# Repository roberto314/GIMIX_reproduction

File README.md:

# GIMIX_reproduction

This Repository is for primarily my GIMIX Ghost Reproduction and various SS-30 and SS-50 Cards.

- GIMIX DMA SASI board finished, no PALs, production ready, gerbers exported

- GIMIX DMA SASI board production version, second Regulator added

- GIMIX dumb two port serial board finished, no PALs, production possible

- Tanner 64k SRAM board finished, no PALs, production possible

- GIMIX Baud Rate Generator Board finished, no PALs, production possible

- GIMIX Floppy DMA finished, no PALs, production possible but not recommended - use production version

- GIMIX Floppy DMA ready for production, cleanup, different routing

- GIMIX intelligent 3-port Serial IO Processor finished (RS232 Transceiver are missing), PAL Contents missing, Firmware found.

- GIMIX Motherboard with onboard Baudrate generator, done, production possible

- GIMIX Motherboard without onboard Baudrate generator, done, production possible

- GIMIX 256k SRAM done, PAL missing but should not be too difficult to figure out, production possible, mods for 62256 chips instead of original 6264. Battery backup won't work with 62256 chips!

- GIMIX 6809 CPU Plus - done, production NOT possible, redesign with GAL or fast EPROM needed, FPLA Contents missing

- GIMIX 6809 CPU Plus Plus - done, This is a production version of the CPU+ board. Changes are: fast EPROM instead of FPLA, one of the four EPROM Sockets is now for a 28-pin EPROM

- GIMIX CRC Generator board - work started but PAL contents missing, schematic missing (a couple of traces need testing), production NOT possible

- GIMIX 6809 CPU III - layout finished but PAL contents missing (some may be registerd - GMX 010 type), production NOT possible

- GIMIX Ghost 6800 - layout finished but some ICs are very rare, production might not be sensible, maybe a redesign with more available components.

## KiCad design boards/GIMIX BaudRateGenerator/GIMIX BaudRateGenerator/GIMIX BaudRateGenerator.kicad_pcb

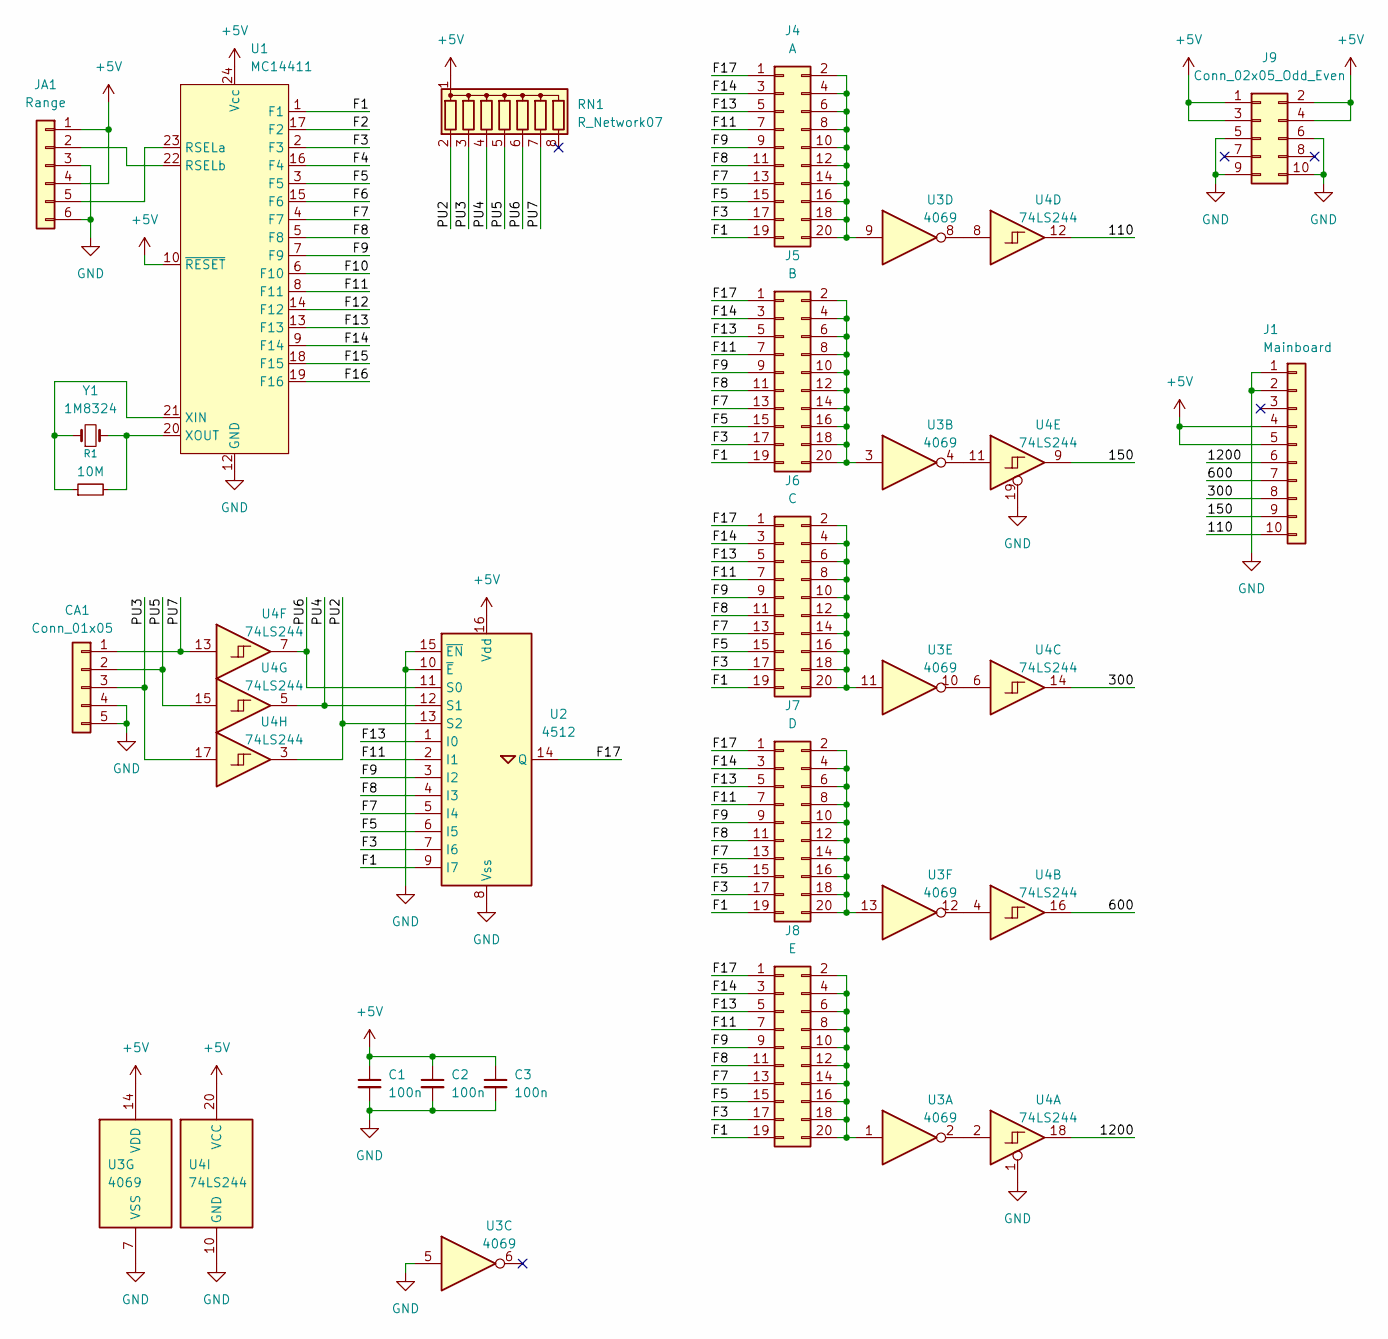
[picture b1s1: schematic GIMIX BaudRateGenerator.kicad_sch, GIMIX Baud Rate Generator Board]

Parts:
C1, C2, C3: 100n; C_Disc_D3.8mm_W2.6mm_P2.50mm
CA1: Conn_01x05; PinHeader_1x05_P2.54mm_Vertical
J1: Mainboard; SS-10_new
J4: A; PinHeader_2x10_P2.54mm_Vertical
J5: B; PinHeader_2x10_P2.54mm_Vertical
J6: C; PinHeader_2x10_P2.54mm_Vertical
J7: D; PinHeader_2x10_P2.54mm_Vertical
J8: E; PinHeader_2x10_P2.54mm_Vertical
J9: Conn_02x05_Odd_Even; PinHeader_2x05_P2.54mm_Vertical
JA1: Range; PinHeader_1x06_P2.54mm_Vertical
R1: 10M; R_Axial_DIN0207_L6.3mm_D2.5mm_P10.16mm_Horizontal
RN1: R_Network07; R_Array_SIP8
U1: MC14411; DIP-24_W15.24mm
U2: 4512; DIP-16_W7.62mm
U3: 4069; DIP-14_W7.62mm
U4: 74LS244; DIP-20_W7.62mm
Y1: 1M8324; Crystal_HC33-U_Horizontal

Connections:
+5V: C1.1, C2.1, C3.1, J1.4, J1.5, J9.1, J9.2, J9.3, J9.4, JA1.1, JA1.4, RN1.1 (common), U1.10 (~RESET), U1.24 (Vcc), U2.16 (Vdd), U3.14 (VDD), U4.20 (VCC)
/110: J1.10, U4.12
/150: J1.9, U4.9
/300: J1.8, U4.14
/600: J1.7, U4.16
/1200: J1.6, U4.18
/F1: J4.19, J5.19, J6.19, J7.19, J8.19, U1.1 (F1), U2.9 (I7)
/F2: U1.17 (F2)
/F3: J4.17, J5.17, J6.17, J7.17, J8.17, U1.2 (F3), U2.7 (I6)
/F4: U1.16 (F4)
/F5: J4.15, J5.15, J6.15, J7.15, J8.15, U1.3 (F5), U2.6 (I5)
/F6: U1.15 (F6)
/F7: J4.13, J5.13, J6.13, J7.13, J8.13, U1.4 (F7), U2.5 (I4)
/F8: J4.11, J5.11, J6.11, J7.11, J8.11, U1.5 (F8), U2.4 (I3)
/F9: J4.9, J5.9, J6.9, J7.9, J8.9, U1.7 (F9), U2.3 (I2)
/F10: U1.6 (F10)
/F11: J4.7, J5.7, J6.7, J7.7, J8.7, U1.8 (F11), U2.2 (I1)
/F12: U1.14 (F12)
/F13: J4.5, J5.5, J6.5, J7.5, J8.5, U1.13 (F13), U2.1 (I0)
/F14: J4.3, J5.3, J6.3, J7.3, J8.3, U1.9 (F14)
/F15: U1.18 (F15)
/F16: U1.19 (F16)
/F17: J4.1, J5.1, J6.1, J7.1, J8.1, U2.14 (Q)
/PU2: RN1.2 (R1), U2.13 (S2), U4.3
/PU3: CA1.3, RN1.3 (R2), U4.17
/PU4: RN1.4 (R3), U2.12 (S1), U4.5
/PU5: CA1.2, RN1.5 (R4), U4.15
/PU6: RN1.6 (R5), U2.11 (S0), U4.7
/PU7: CA1.1, RN1.7 (R6), U4.13
GND: C1.2, C2.2, C3.2, CA1.4, CA1.5, J1.1, J1.2, J9.5, J9.6, J9.9, J9.10, JA1.3, JA1.6, U1.12 (GND), U2.8 (Vss), U2.10 (~E), U2.15 (~EN), U3.5, U3.7 (VSS), U4.1, U4.10 (GND), U4.19
unnamed: J4.2, J4.4, J4.6, J4.8, J4.10, J4.12, J4.14, J4.16, J4.18, J4.20, U3.9
unnamed: J5.2, J5.4, J5.6, J5.8, J5.10, J5.12, J5.14, J5.16, J5.18, J5.20, U3.3
unnamed: J6.2, J6.4, J6.6, J6.8, J6.10, J6.12, J6.14, J6.16, J6.18, J6.20, U3.11
unnamed: J7.2, J7.4, J7.6, J7.8, J7.10, J7.12, J7.14, J7.16, J7.18, J7.20, U3.13
unnamed: J8.2, J8.4, J8.6, J8.8, J8.10, J8.12, J8.14, J8.16, J8.18, J8.20, U3.1
unnamed: JA1.2, U1.22 (RSELb)
unnamed: JA1.5, U1.23 (RSELa)
unnamed: R1.1, U1.21 (XIN), Y1.1
unnamed: R1.2, U1.20 (XOUT), Y1.2
unnamed: U3.2, U4.2
unnamed: U3.4, U4.11
unnamed: U3.8, U4.8
unnamed: U3.10, U4.6
unnamed: U3.12, U4.4

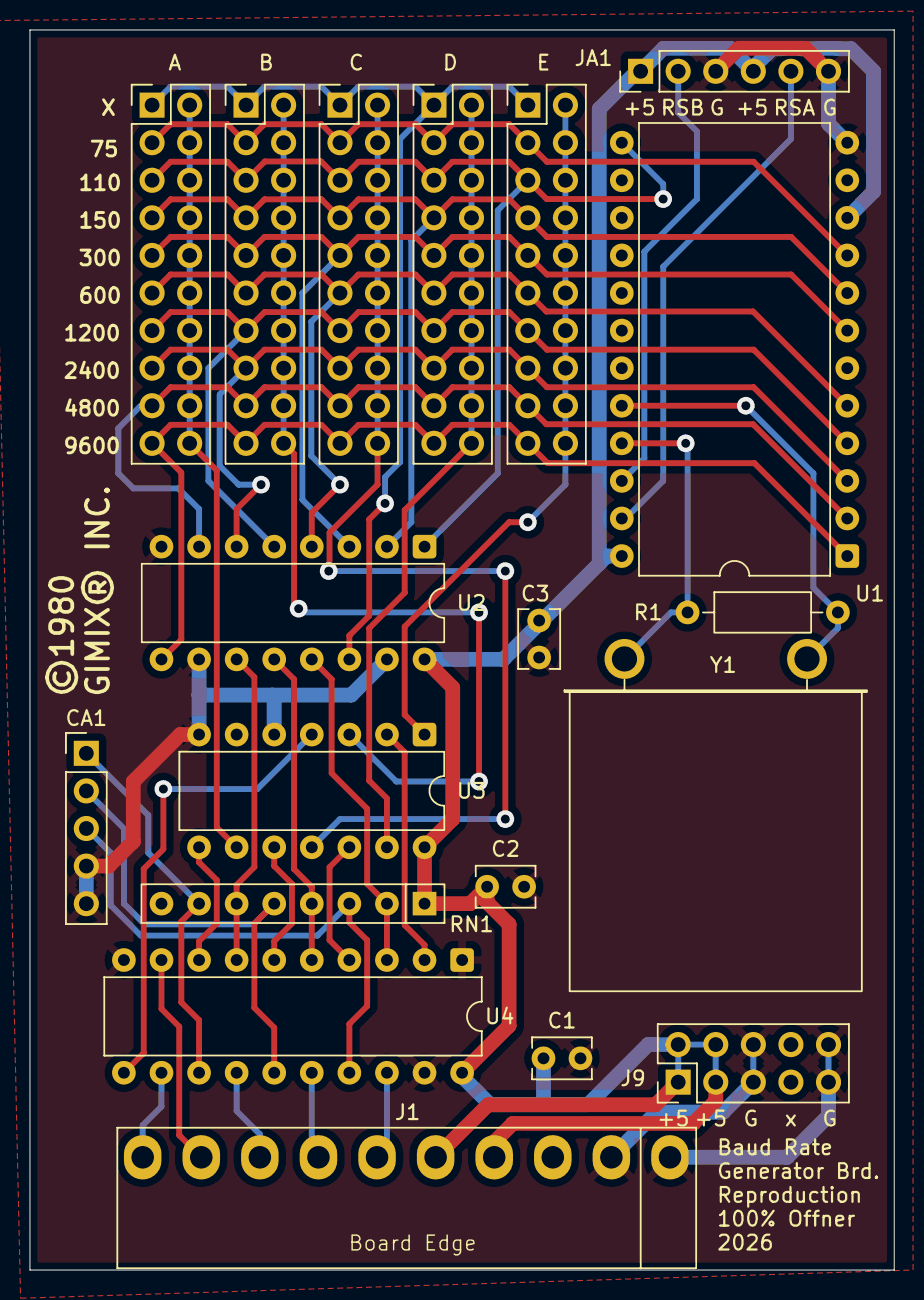
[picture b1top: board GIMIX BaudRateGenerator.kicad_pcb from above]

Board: 2 copper layers, 58.4 x 83.8 mm, 19 parts (0 on the bottom side), 37 nets.

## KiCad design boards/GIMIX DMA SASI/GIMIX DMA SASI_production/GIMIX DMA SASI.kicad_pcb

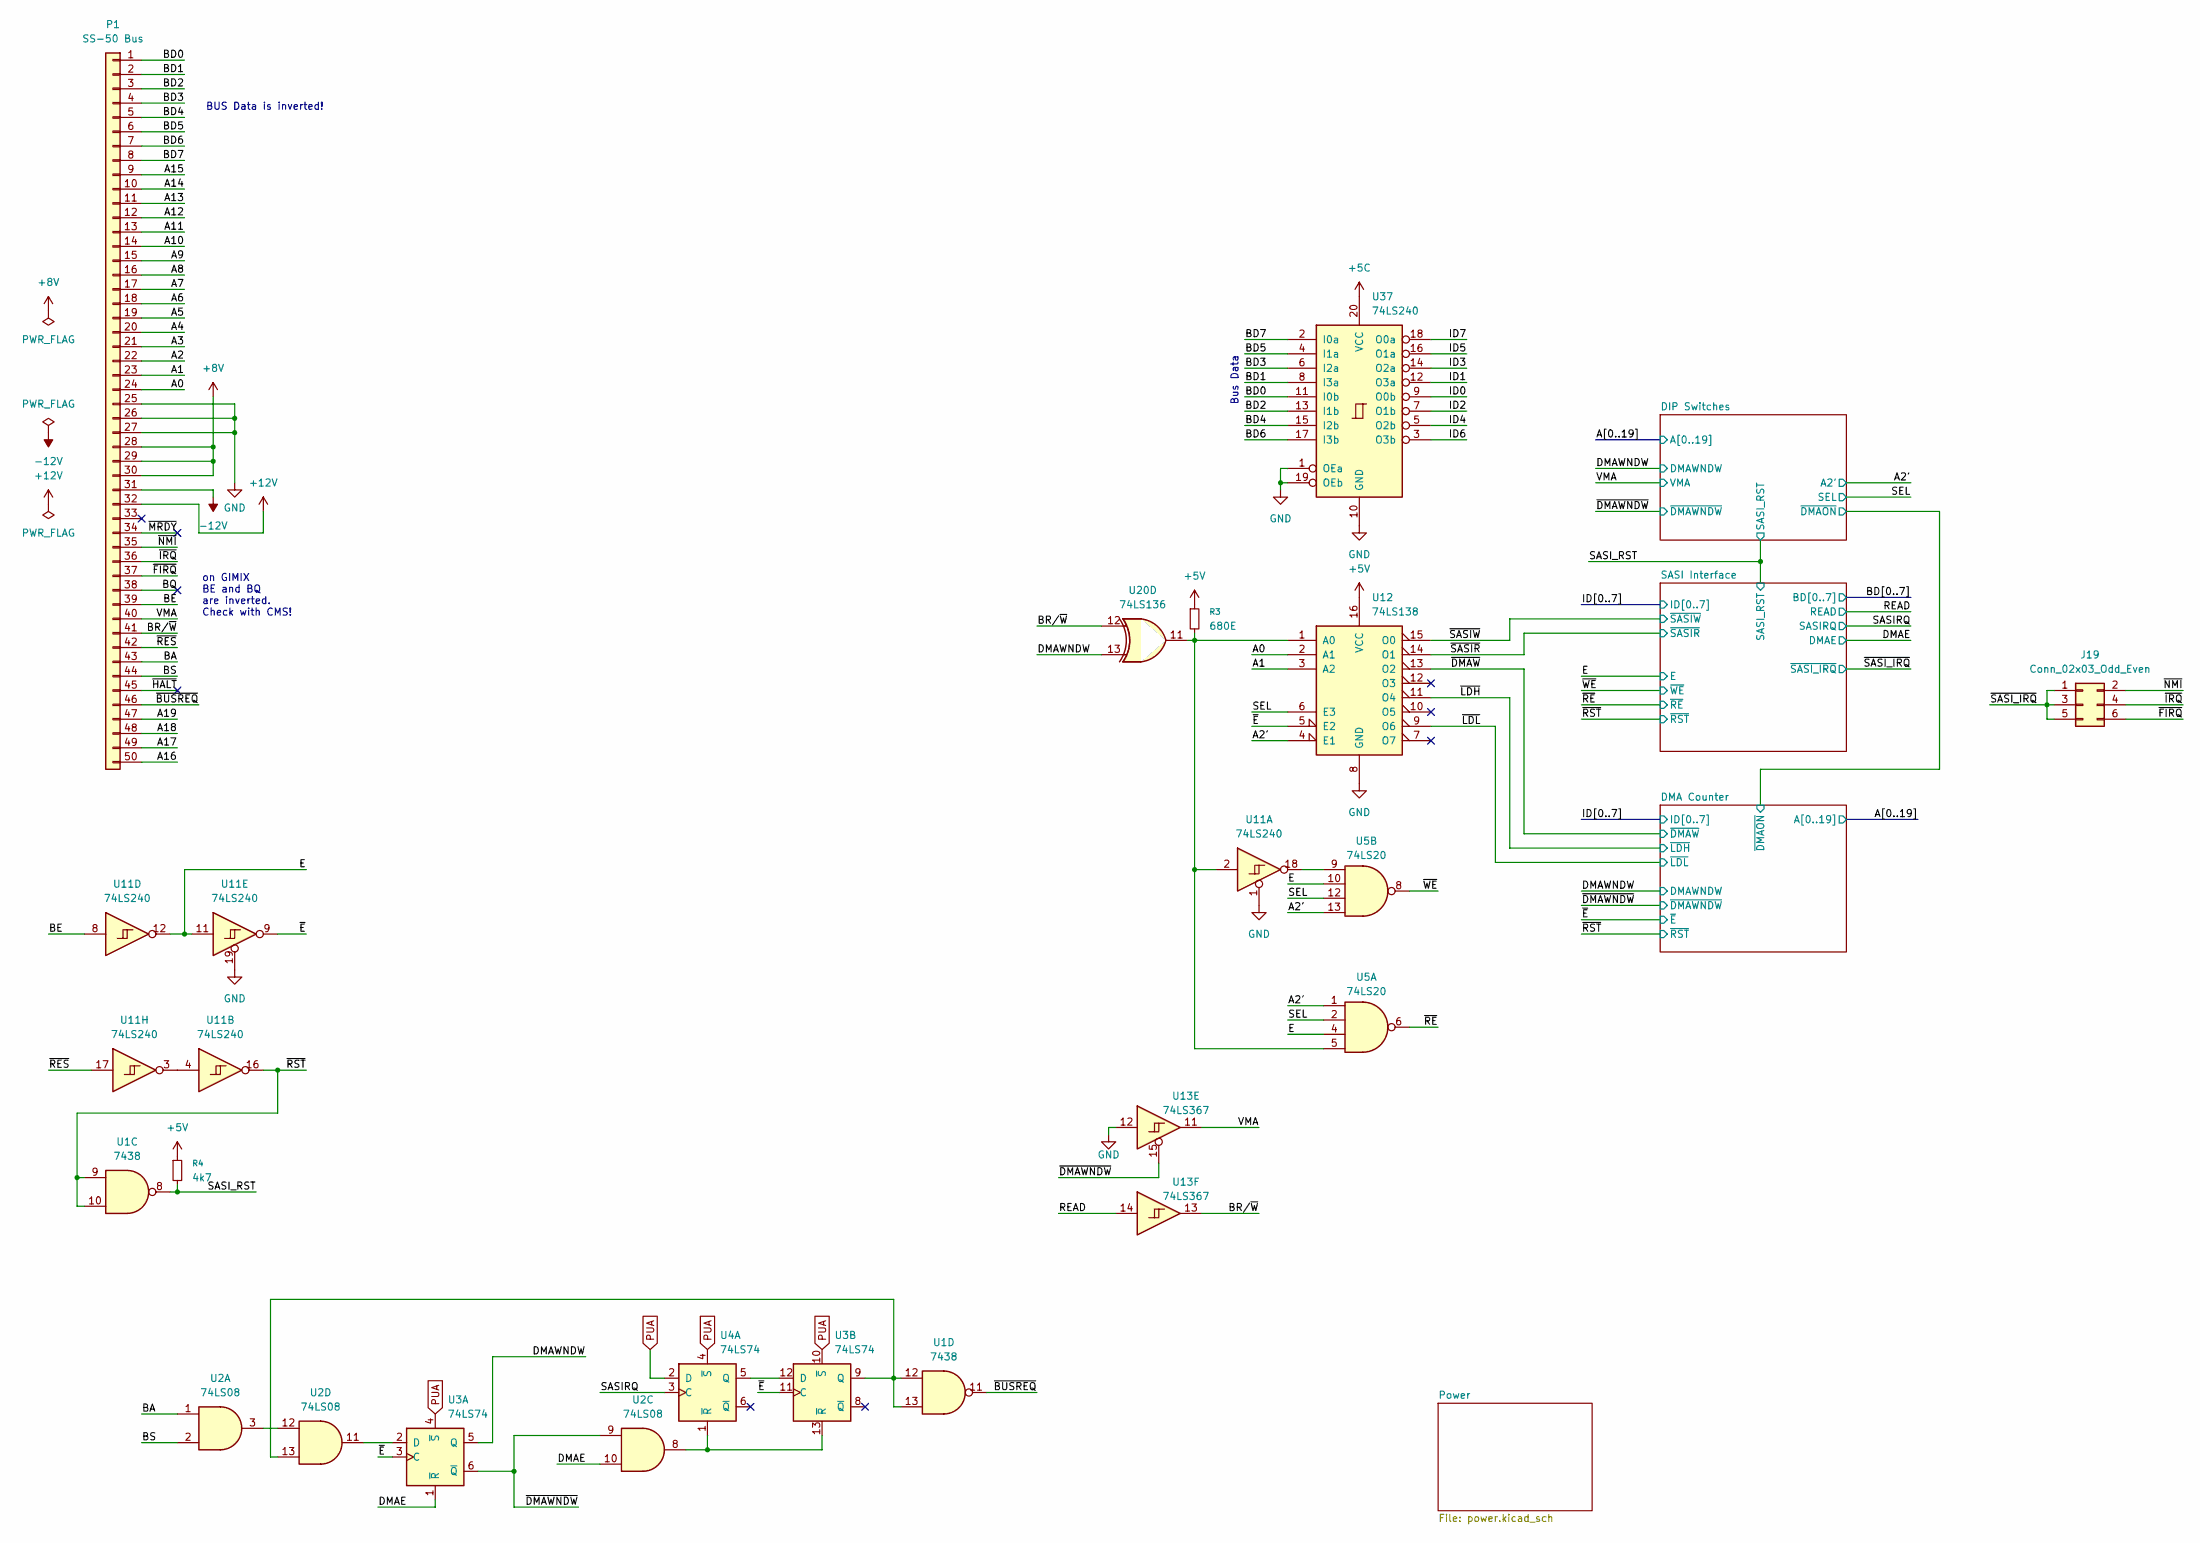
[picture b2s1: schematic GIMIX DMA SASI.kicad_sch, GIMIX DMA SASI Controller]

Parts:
J19: Conn_02x03_Odd_Even; PinHeader_2x03_P2.54mm_Vertical
P1: SS-50 Bus; SS-50_new
R3: 680E; R_Axial_DIN0411_L9.9mm_D3.6mm_P12.70mm_Horizontal
R4: 4k7; R_Axial_DIN0411_L9.9mm_D3.6mm_P12.70mm_Horizontal
U1: 7438; DIP-14_W7.62mm
U2: 74LS08; DIP-14_W7.62mm
U3, U4: 74LS74; DIP-14_W7.62mm
U5: 74LS20; DIP-14_W7.62mm
U11, U37: 74LS240; DIP-20_W7.62mm
U12: 74LS138; DIP-16_W7.62mm
U13: 74LS367; DIP-16_W7.62mm
U20: 74LS136; DIP-14_W7.62mm

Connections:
+5C: U37.20 (VCC); also elsewhere on the board
+5V: R3.1, R4.1, U12.16 (VCC); also elsewhere on the board
+8V: P1.28, P1.29, P1.30; also elsewhere on the board
+12V: P1.32
-12V: P1.31
/A0: P1.24, U12.2 (A1); also elsewhere on the board
/A1: P1.23, U12.3 (A2); also elsewhere on the board
/A2: P1.22; also elsewhere on the board
/A2': U5.1, U5.13, U12.4 (E1); also elsewhere on the board
/A3: P1.21; also elsewhere on the board
/A4: P1.20; also elsewhere on the board
/A5: P1.19; also elsewhere on the board
/A6: P1.18; also elsewhere on the board
/A7: P1.17; also elsewhere on the board
/A8: P1.16; also elsewhere on the board
/A9: P1.15; also elsewhere on the board
/A10: P1.14; also elsewhere on the board
/A11: P1.13; also elsewhere on the board
/A12: P1.12; also elsewhere on the board
/A13: P1.11; also elsewhere on the board
/A14: P1.10; also elsewhere on the board
/A15: P1.9; also elsewhere on the board
/A16: P1.50; also elsewhere on the board
/A17: P1.49; also elsewhere on the board
/A18: P1.48; also elsewhere on the board
/A19: P1.47; also elsewhere on the board
/BA: P1.43, U2.1
/BD0: P1.1, U37.11 (I0b); also elsewhere on the board
/BD1: P1.2, U37.8 (I3a); also elsewhere on the board
/BD2: P1.3, U37.13 (I1b); also elsewhere on the board
/BD3: P1.4, U37.6 (I2a); also elsewhere on the board
/BD4: P1.5, U37.15 (I2b); also elsewhere on the board
/BD5: P1.6, U37.4 (I1a); also elsewhere on the board
/BD6: P1.7, U37.17 (I3b); also elsewhere on the board
/BD7: P1.8, U37.2 (I0a); also elsewhere on the board
/BE: P1.39, U11.8
/BQ: P1.38
/BR/~W: P1.41, U13.13, U20.12
/BS: P1.44, U2.2
/DMAE: U2.10, U3.1 (~R); also elsewhere on the board
/DMAWNDW: U3.5 (Q), U20.13; also elsewhere on the board
/E: U5.4, U5.10, U11.11, U11.12; also elsewhere on the board
/ID0: U37.9 (O0b); also elsewhere on the board
/ID1: U37.12 (O3a); also elsewhere on the board
/ID2: U37.7 (O1b); also elsewhere on the board
/ID3: U37.14 (O2a); also elsewhere on the board
/ID4: U37.5 (O2b); also elsewhere on the board
/ID5: U37.16 (O1a); also elsewhere on the board
/ID6: U37.3 (O3b); also elsewhere on the board
/ID7: U37.18 (O0a); also elsewhere on the board
/READ: U13.14; also elsewhere on the board
/SASIRQ: U4.3 (C); also elsewhere on the board
/SASI_RST: R4.2, U1.8; also elsewhere on the board
/SEL: U5.2, U5.12, U12.6 (E3); also elsewhere on the board
/VMA: P1.40, U13.11; also elsewhere on the board
/~BUSREQ: P1.46, U1.11
/~DMAWNDW: U2.9, U3.6 (~Q), U13.15; also elsewhere on the board
/~DMAW: U12.13 (O2); also elsewhere on the board
/~E: U3.3 (C), U3.11 (C), U11.9, U12.5 (E2); also elsewhere on the board
/~FIRQ: J19.6, P1.37
/~HALT: P1.45
/~IRQ: J19.4, P1.36
/~LDH: U12.11 (O4); also elsewhere on the board
/~LDL: U12.9 (O6); also elsewhere on the board
/~MRDY: P1.34
/~NMI: J19.2, P1.35
/~RES: P1.42, U11.17
/~RE: U5.6; also elsewhere on the board
/~RST: U1.9, U1.10, U11.16; also elsewhere on the board
/~SASIR: U12.14 (O1); also elsewhere on the board
/~SASIW: U12.15 (O0); also elsewhere on the board
/~SASI_IRQ: J19.1, J19.3, J19.5; also elsewhere on the board
/~WE: U5.8; also elsewhere on the board
GND: P1.25, P1.26, P1.27, U11.1, U11.19, U12.8 (GND), U13.12, U37.1 (OEa), U37.10 (GND), U37.19 (OEb); also elsewhere on the board
unnamed: U2.3, U2.12
unnamed: U2.11, U3.2 (D)
unnamed: U3.12 (D), U4.5 (Q)
unnamed: U1.12, U1.13, U2.13, U3.9 (Q)
unnamed: U2.8, U3.13 (~R), U4.1 (~R)
unnamed: U11.3, U11.4
unnamed: U5.9, U11.18
unnamed: R3.2, U5.5, U11.2, U12.1 (A0), U20.11
PUA: U3.4 (~S), U3.10 (~S), U4.2 (D), U4.4 (~S); also elsewhere on the board

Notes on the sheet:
on GIMIX BE and BQ are inverted. Check with CMS!
Bus Data
BUS Data is inverted!

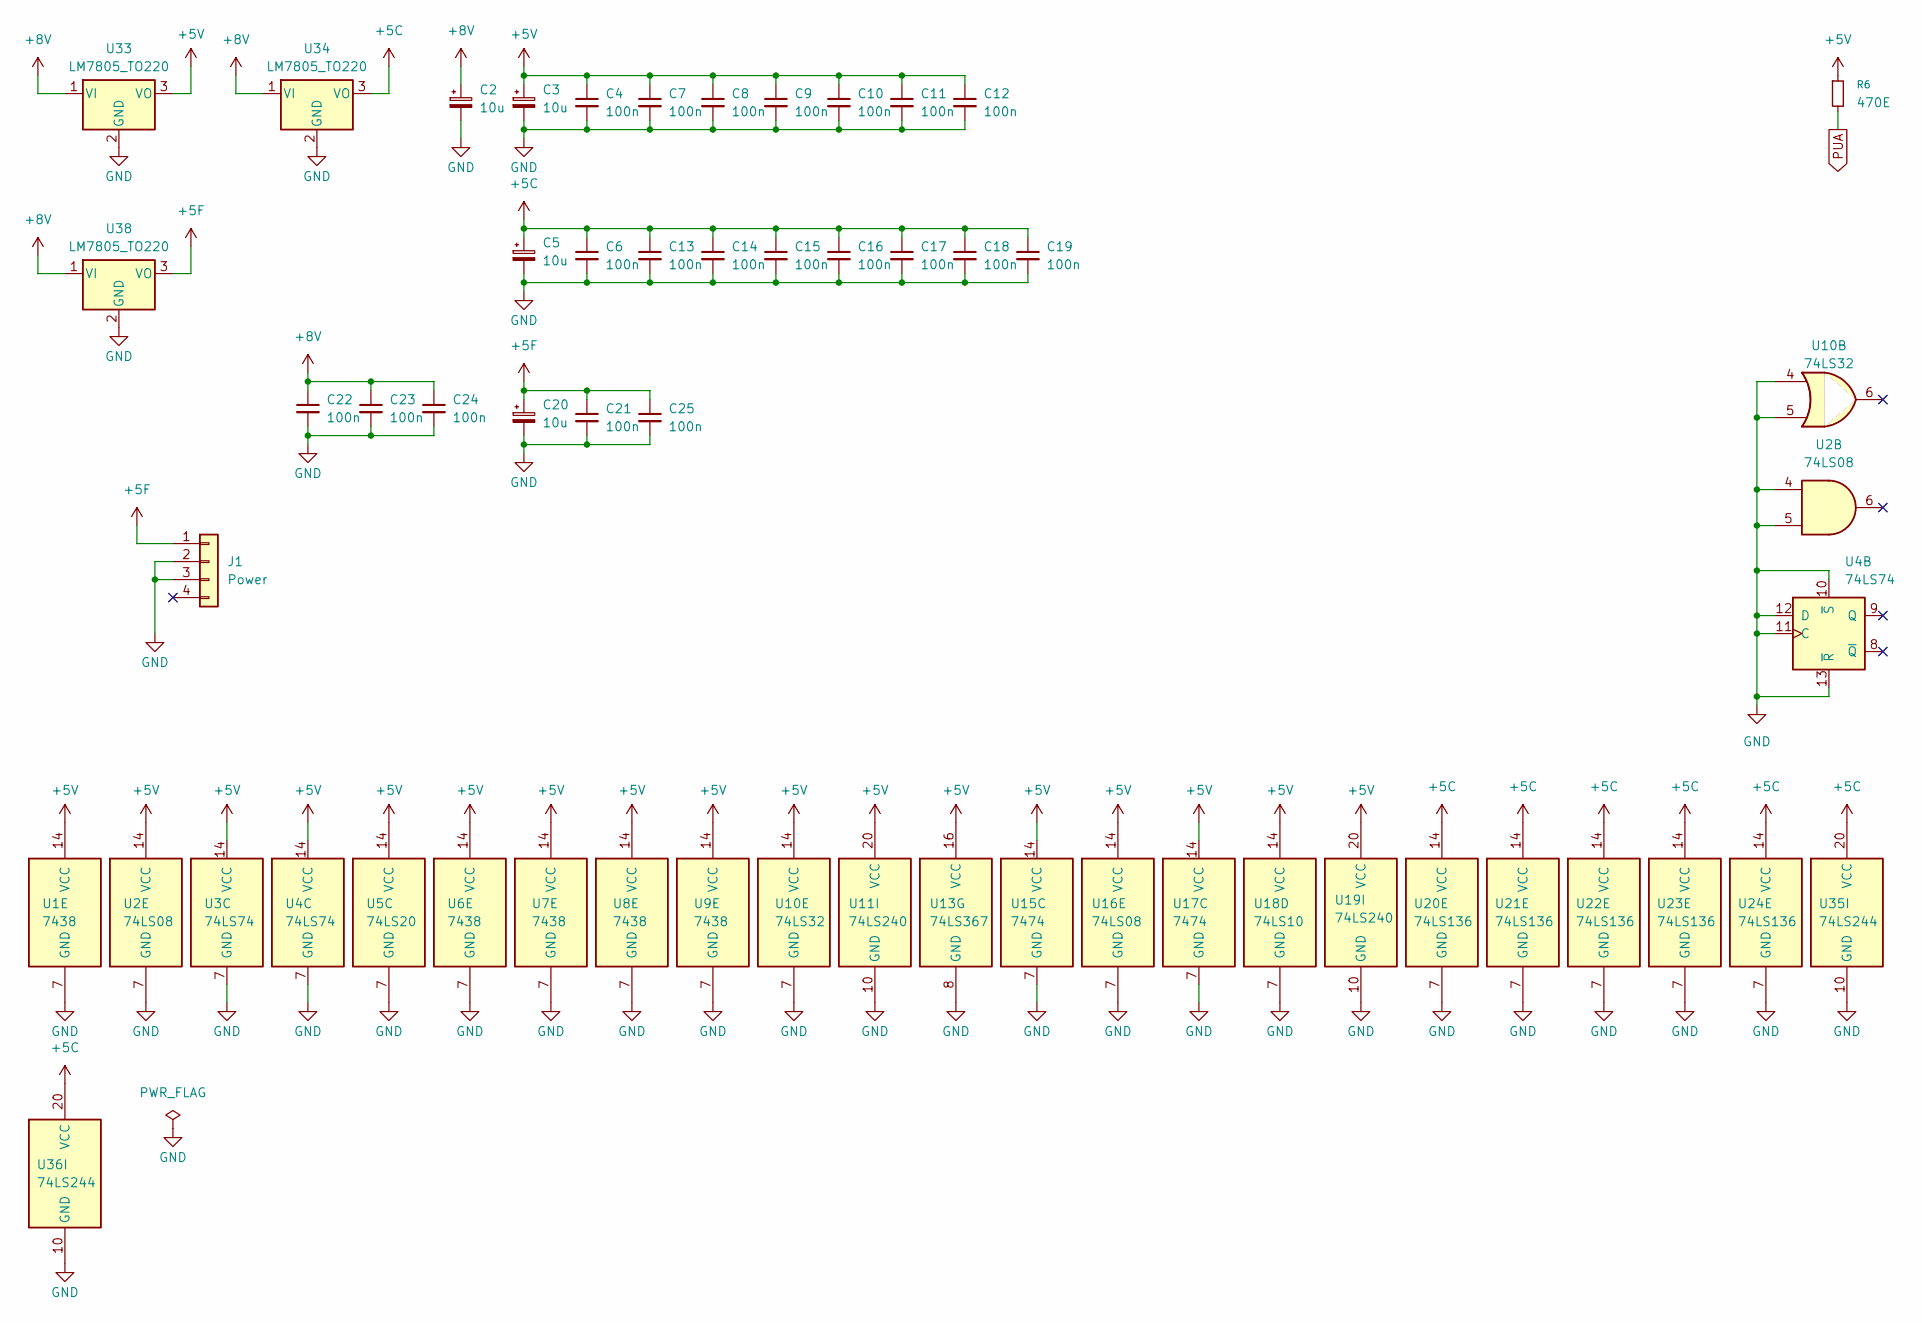
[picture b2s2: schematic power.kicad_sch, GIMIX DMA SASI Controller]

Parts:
C2: 10u; CP_Radial_D12.5mm_P5.00mm
C3, C5, C20: 10u; CP_Radial_D5.0mm_P2.50mm
C4, C6, C7, C8, C9, C10, C11, C12, C13, C14, C15, C16, C17, C18, C19, C21, C22, C23, C24, C25: 100n; C_Disc_D3.0mm_W1.6mm_P2.50mm
J1: Power; PinHeader_1x04_P2.54mm_Vertical
R6: 470E; R_Axial_DIN0411_L9.9mm_D3.6mm_P12.70mm_Horizontal
U1, U6, U7, U8, U9: 7438; DIP-14_W7.62mm
U2, U16: 74LS08; DIP-14_W7.62mm
U3, U4: 74LS74; DIP-14_W7.62mm
U5: 74LS20; DIP-14_W7.62mm
U10: 74LS32; DIP-14_W7.62mm
U11, U19: 74LS240; DIP-20_W7.62mm
U13: 74LS367; DIP-16_W7.62mm
U15, U17: 7474; DIP-14_W7.62mm
U18: 74LS10; DIP-14_W7.62mm
U20, U21, U22, U23, U24: 74LS136; DIP-14_W7.62mm
U33, U34, U38: LM7805_TO220; TO-220-3_Horizontal_TabDown
U35, U36: 74LS244; DIP-20_W7.62mm

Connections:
+5C: C5.1, C6.1, C13.1, C14.1, C15.1, C16.1, C17.1, C18.1, C19.1, U20.14 (VCC), U21.14 (VCC), U22.14 (VCC), U23.14 (VCC), U24.14 (VCC), U34.3 (VO), U35.20 (VCC), U36.20 (VCC); also elsewhere on the board
+5F: C20.1, C21.1, C25.1, J1.1, U38.3 (VO)
+5V: C3.1, C4.1, C7.1, C8.1, C9.1, C10.1, C11.1, C12.1, R6.1, U1.14 (VCC), U2.14 (VCC), U3.14 (VCC), U4.14 (VCC), U5.14 (VCC), U6.14 (VCC), U7.14 (VCC), U8.14 (VCC), U9.14 (VCC), U10.14 (VCC), U11.20 (VCC), U13.16 (VCC), U15.14 (VCC), U16.14 (VCC), U17.14 (VCC), U18.14 (VCC), U19.20 (VCC), U33.3 (VO); also elsewhere on the board
+8V: C2.1, C22.1, C23.1, C24.1, U33.1 (VI), U34.1 (VI), U38.1 (VI); also elsewhere on the board
GND: C2.2, C3.2, C4.2, C5.2, C6.2, C7.2, C8.2, C9.2, C10.2, C11.2, C12.2, C13.2, C14.2, C15.2, C16.2, C17.2, C18.2, C19.2, C20.2, C21.2, C22.2, C23.2, C24.2, C25.2, J1.2, J1.3, U1.7 (GND), U2.4, U2.5, U2.7 (GND), U3.7 (GND), U4.7 (GND), U4.10 (~S), U4.11 (C), U4.12 (D), U4.13 (~R), U5.7 (GND), U6.7 (GND), U7.7 (GND), U8.7 (GND), U9.7 (GND), U10.4, U10.5, U10.7 (GND), U11.10 (GND), U13.8 (GND), U15.7 (GND), U16.7 (GND), U17.7 (GND), U18.7 (GND), U19.10 (GND), U20.7 (GND), U21.7 (GND), U22.7 (GND), U23.7 (GND), U24.7 (GND), U33.2 (GND), U34.2 (GND), U35.10 (GND), U36.10 (GND), U38.2 (GND); also elsewhere on the board
PUA: R6.2; also elsewhere on the board

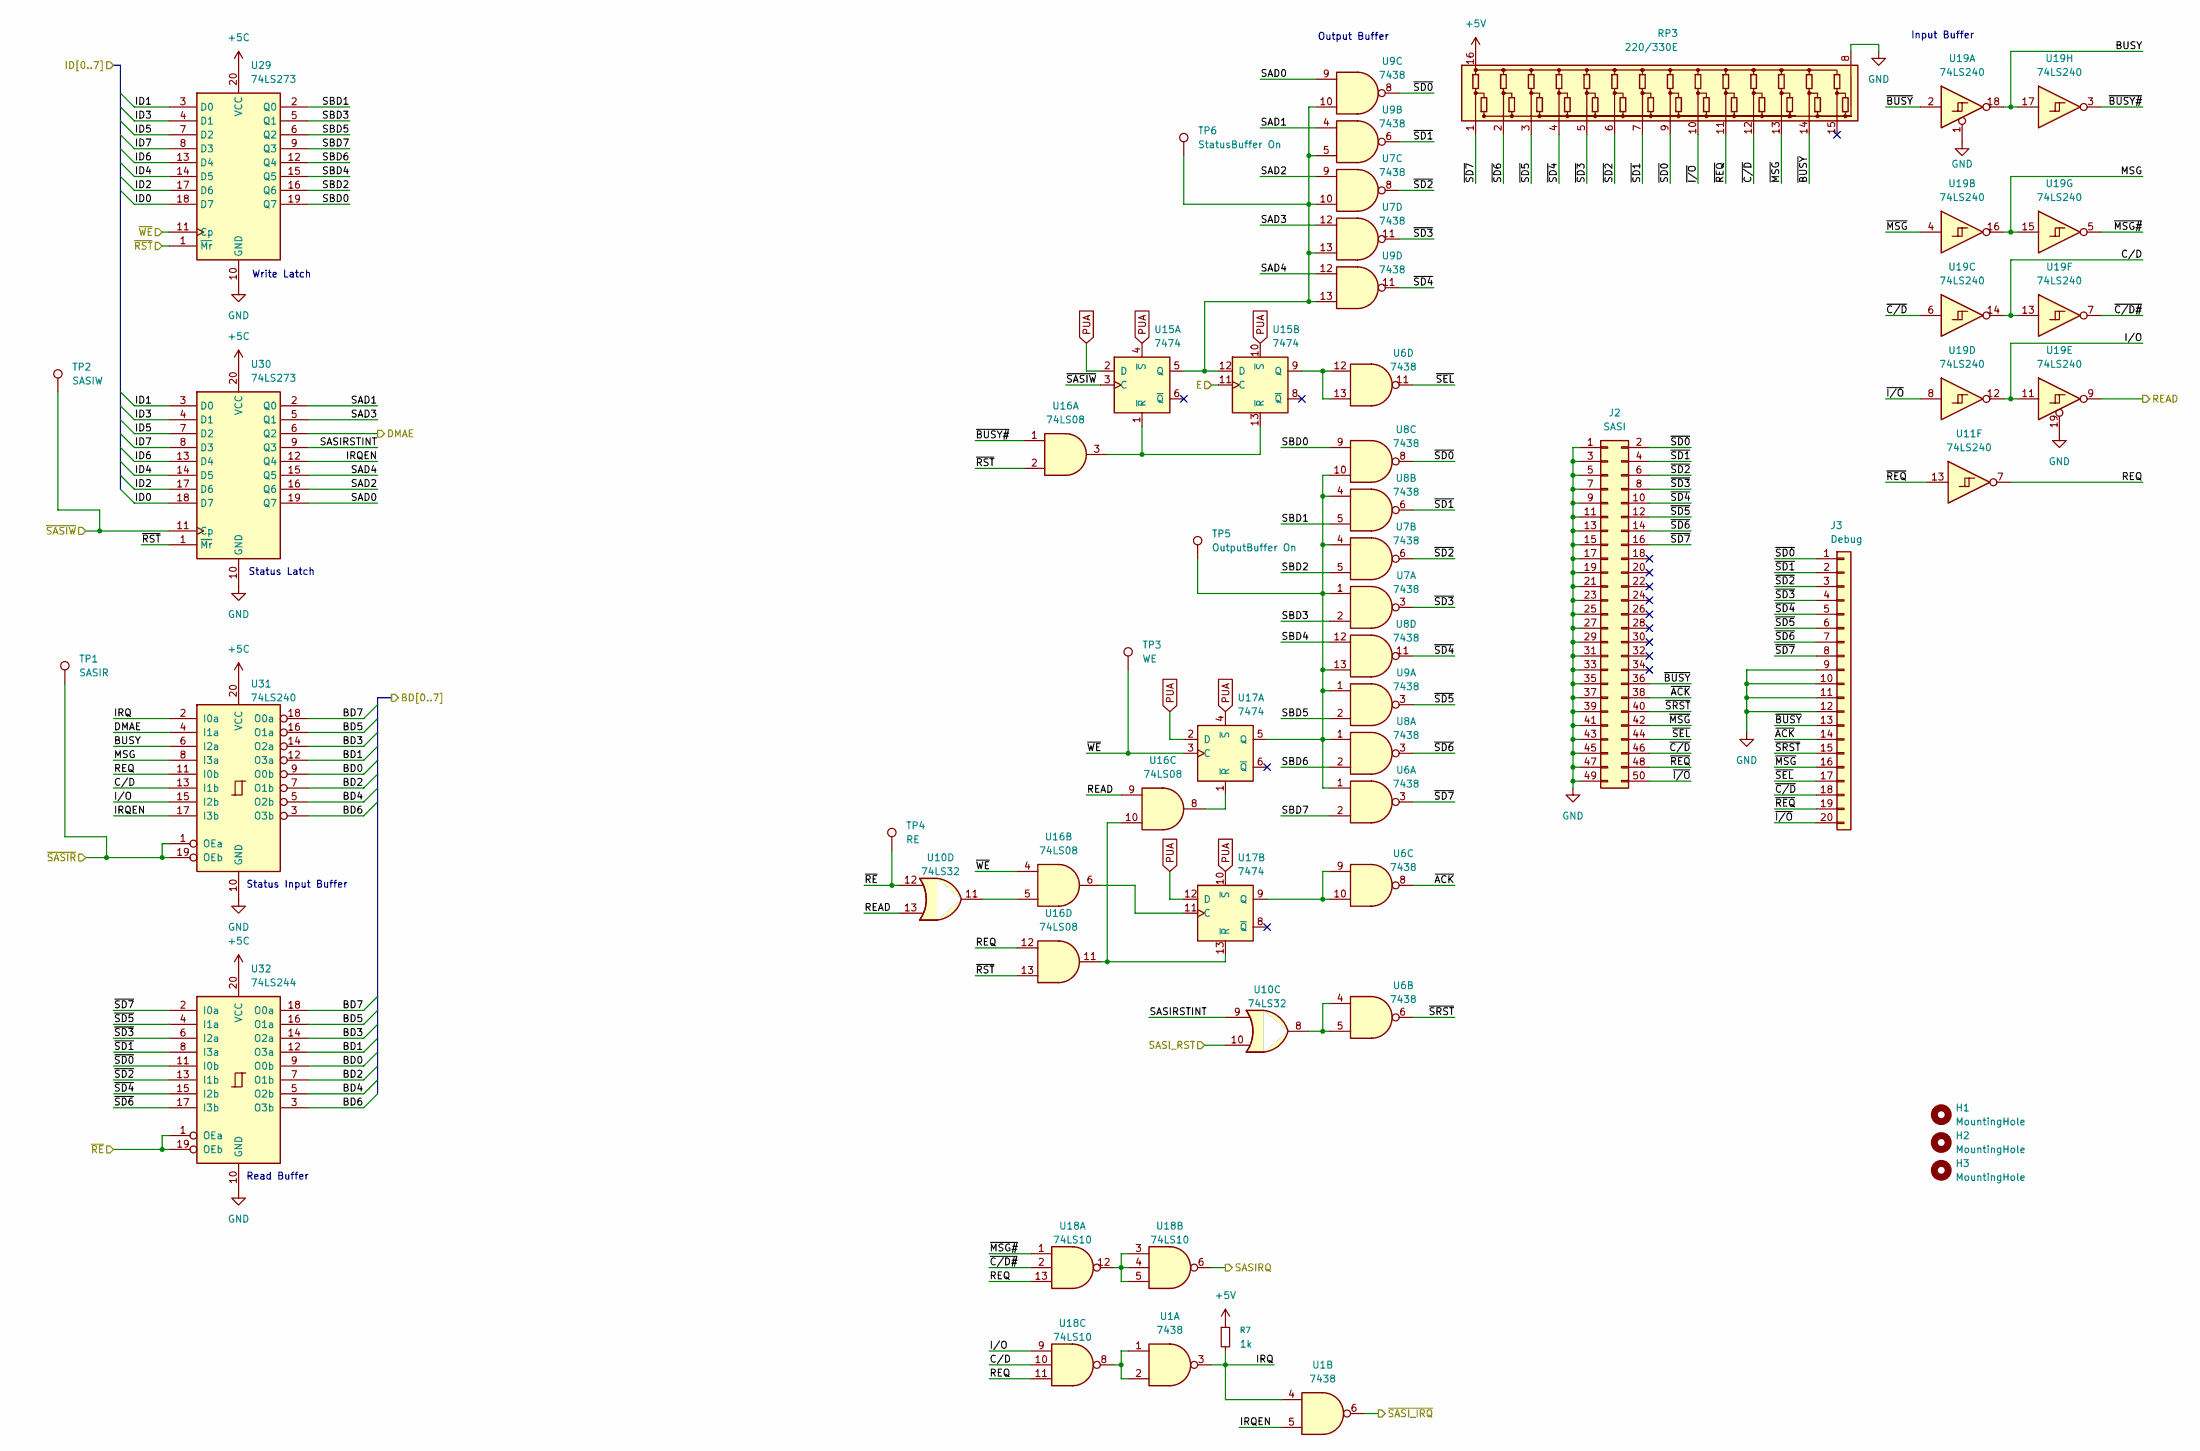
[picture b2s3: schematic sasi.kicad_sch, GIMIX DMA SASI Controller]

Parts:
H1, H2, H3: MountingHole; MountingHole_3.2mm_M3_ISO14580
J2: SASI; PinHeader_2x25_P2.54mm_Horizontal
J3: Debug; PinHeader_1x20_P2.54mm_Vertical
R7: 1k; R_Axial_DIN0411_L9.9mm_D3.6mm_P12.70mm_Horizontal
RP3: 220/330E; DIP-16_W7.62mm
TP1: SASIR; PinHeader_1x01_P2.54mm_Vertical
TP2: SASIW; PinHeader_1x01_P2.54mm_Vertical
TP3: WE; PinHeader_1x01_P2.54mm_Vertical
TP4: RE; PinHeader_1x01_P2.54mm_Vertical
TP5: OutputBuffer On; PinHeader_1x01_P2.54mm_Vertical
TP6: StatusBuffer On; PinHeader_1x01_P2.54mm_Vertical
U1, U6, U7, U8, U9: 7438; DIP-14_W7.62mm
U10: 74LS32; DIP-14_W7.62mm
U11, U19, U31: 74LS240; DIP-20_W7.62mm
U15, U17: 7474; DIP-14_W7.62mm
U16: 74LS08; DIP-14_W7.62mm
U18: 74LS10; DIP-14_W7.62mm
U29, U30: 74LS273; DIP-20_W7.62mm
U32: 74LS244; DIP-20_W7.62mm

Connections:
+5C: U29.20 (VCC), U30.20 (VCC), U31.20 (VCC), U32.20 (VCC); also elsewhere on the board
+5V: R7.1, RP3.16 (COM1); also elsewhere on the board
/BD0: U31.9 (O0b), U32.9 (O0b); also elsewhere on the board
/BD1: U31.12 (O3a), U32.12 (O3a); also elsewhere on the board
/BD2: U31.7 (O1b), U32.7 (O1b); also elsewhere on the board
/BD3: U31.14 (O2a), U32.14 (O2a); also elsewhere on the board
/BD4: U31.5 (O2b), U32.5 (O2b); also elsewhere on the board
/BD5: U31.16 (O1a), U32.16 (O1a); also elsewhere on the board
/BD6: U31.3 (O3b), U32.3 (O3b); also elsewhere on the board
/BD7: U31.18 (O0a), U32.18 (O0a); also elsewhere on the board
/DMAE: U30.6 (Q2), U31.4 (I1a); also elsewhere on the board
/E: U15.11 (C); also elsewhere on the board
/ID0: U29.18 (D7), U30.18 (D7); also elsewhere on the board
/ID1: U29.3 (D0), U30.3 (D0); also elsewhere on the board
/ID2: U29.17 (D6), U30.17 (D6); also elsewhere on the board
/ID3: U29.4 (D1), U30.4 (D1); also elsewhere on the board
/ID4: U29.14 (D5), U30.14 (D5); also elsewhere on the board
/ID5: U29.7 (D2), U30.7 (D2); also elsewhere on the board
/ID6: U29.13 (D4), U30.13 (D4); also elsewhere on the board
/ID7: U29.8 (D3), U30.8 (D3); also elsewhere on the board
/READ: U10.13, U16.9, U19.9; also elsewhere on the board
/SASI Interface/BUSY: U19.17, U19.18, U31.6 (I2a)
/SASI Interface/C/D: U18.10, U19.13, U19.14, U31.13 (I1b)
/SASI Interface/IRQ: R7.2, U1.3, U1.4, U31.2 (I0a)
/SASI Interface/IRQEN: U1.5, U30.12 (Q4), U31.17 (I3b)
/SASI Interface/I/O: U18.9, U19.11, U19.12, U31.15 (I2b)
/SASI Interface/MSG: U19.15, U19.16, U31.8 (I3a)
/SASI Interface/REQ: U11.7, U16.12, U18.11, U18.13, U31.11 (I0b)
/SASI Interface/SAD0: U9.9, U30.19 (Q7)
/SASI Interface/SAD1: U9.4, U30.2 (Q0)
/SASI Interface/SAD2: U7.9, U30.16 (Q6)
/SASI Interface/SAD3: U7.12, U30.5 (Q1)
/SASI Interface/SAD4: U9.12, U30.15 (Q5)
/SASI Interface/SASIRSTINT: U10.9, U30.9 (Q3)
/SASI Interface/SBD0: U8.9, U29.19 (Q7)
/SASI Interface/SBD1: U8.5, U29.2 (Q0)
/SASI Interface/SBD2: U7.5, U29.16 (Q6)
/SASI Interface/SBD3: U7.2, U29.5 (Q1)
/SASI Interface/SBD4: U8.12, U29.15 (Q5)
/SASI Interface/SBD5: U9.2, U29.6 (Q2)
/SASI Interface/SBD6: U8.2, U29.12 (Q4)
/SASI Interface/SBD7: U6.2, U29.9 (Q3)
/SASI Interface/~ACK: J2.38, J3.14, U6.8
/SASI Interface/~BUSY#: U16.1, U19.3
/SASI Interface/~BUSY: J2.36, J3.13, RP3.14 (R13), U19.2
/SASI Interface/~C/D#: U18.2, U19.7
/SASI Interface/~C/D: J2.46, J3.18, RP3.12 (R11), U19.6
/SASI Interface/~I/O: J2.50, J3.20, RP3.10 (R9), U19.8
/SASI Interface/~MSG#: U18.1, U19.5
/SASI Interface/~MSG: J2.42, J3.16, RP3.13 (R12), U19.4
/SASI Interface/~REQ: J2.48, J3.19, RP3.11 (R10), U11.13
/SASI Interface/~SD0: J2.2, J3.1, RP3.9 (R8), U8.8, U9.8, U32.11 (I0b)
/SASI Interface/~SD1: J2.4, J3.2, RP3.7 (R7), U8.6, U9.6, U32.8 (I3a)
/SASI Interface/~SD2: J2.6, J3.3, RP3.6 (R6), U7.6, U7.8, U32.13 (I1b)
/SASI Interface/~SD3: J2.8, J3.4, RP3.5 (R5), U7.3, U7.11, U32.6 (I2a)
/SASI Interface/~SD4: J2.10, J3.5, RP3.4 (R4), U8.11, U9.11, U32.15 (I2b)
/SASI Interface/~SD5: J2.12, J3.6, RP3.3 (R3), U9.3, U32.4 (I1a)
/SASI Interface/~SD6: J2.14, J3.7, RP3.2 (R2), U8.3, U32.17 (I3b)
/SASI Interface/~SD7: J2.16, J3.8, RP3.1 (R1), U6.3, U32.2 (I0a)
/SASI Interface/~SEL: J2.44, J3.17, U6.11
/SASI Interface/~SRST: J2.40, J3.15, U6.6
/SASIRQ: U18.6; also elsewhere on the board
/SASI_RST: U10.10; also elsewhere on the board
/~RE: TP4.1, U10.12, U32.1 (OEa), U32.19 (OEb); also elsewhere on the board
/~RST: U16.2, U16.13, U29.1 (~Mr), U30.1 (~Mr); also elsewhere on the board
/~SASIR: TP1.1, U31.1 (OEa), U31.19 (OEb); also elsewhere on the board
/~SASIW: TP2.1, U15.3 (C), U30.11 (Cp); also elsewhere on the board
/~SASI_IRQ: U1.6; also elsewhere on the board
/~WE: TP3.1, U16.4, U17.3 (C), U29.11 (Cp); also elsewhere on the board
GND: J2.1, J2.3, J2.5, J2.7, J2.9, J2.11, J2.13, J2.15, J2.17, J2.19, J2.21, J2.23, J2.25, J2.27, J2.29, J2.31, J2.33, J2.35, J2.37, J2.39, J2.41, J2.43, J2.45, J2.47, J2.49, J3.9, J3.10, J3.11, J3.12, RP3.8 (COM2), U19.1, U19.19, U29.10 (GND), U30.10 (GND), U31.10 (GND), U32.10 (GND); also elsewhere on the board
unnamed: U1.1, U1.2, U18.8
unnamed: U6.4, U6.5, U10.8
unnamed: U10.11, U16.5
unnamed: TP6.1, U7.10, U7.13, U9.5, U9.10, U9.13, U15.5 (Q), U15.12 (D)
unnamed: U15.1 (~R), U15.13 (~R), U16.3
unnamed: U6.12, U6.13, U15.9 (Q)
unnamed: TP5.1, U6.1, U7.1, U7.4, U8.1, U8.4, U8.10, U8.13, U9.1, U17.5 (Q)
unnamed: U16.8, U17.1 (~R)
unnamed: U16.6, U17.11 (C)
unnamed: U6.9, U6.10, U17.9 (Q)
unnamed: U16.10, U16.11, U17.13 (~R)
unnamed: U18.3, U18.4, U18.5, U18.12
PUA: U15.2 (D), U15.4 (~S), U15.10 (~S), U17.2 (D), U17.4 (~S), U17.10 (~S), U17.12 (D); also elsewhere on the board

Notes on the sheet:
Status Input Buffer
Input Buffer
Read Buffer
Status Latch
Output Buffer
Write Latch

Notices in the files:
boards/GIMIX BaudRateGenerator/GIMIX BaudRateGenerator/GIMIX BaudRateGenerator.kicad_pcb:
©1980
boards/GIMIX DMA Floppy/GIMIX DMA Floppy/GIMIX DMA Floppy.kicad_pcb:
©1983 GIMIX INC.
boards/GIMIX DMA SASI/GIMIX DMA SASI_production/GIMIX DMA SASI.kicad_pcb:
SASI DMA INTERFACE  ©1982 GIMIX® INC Chicago
